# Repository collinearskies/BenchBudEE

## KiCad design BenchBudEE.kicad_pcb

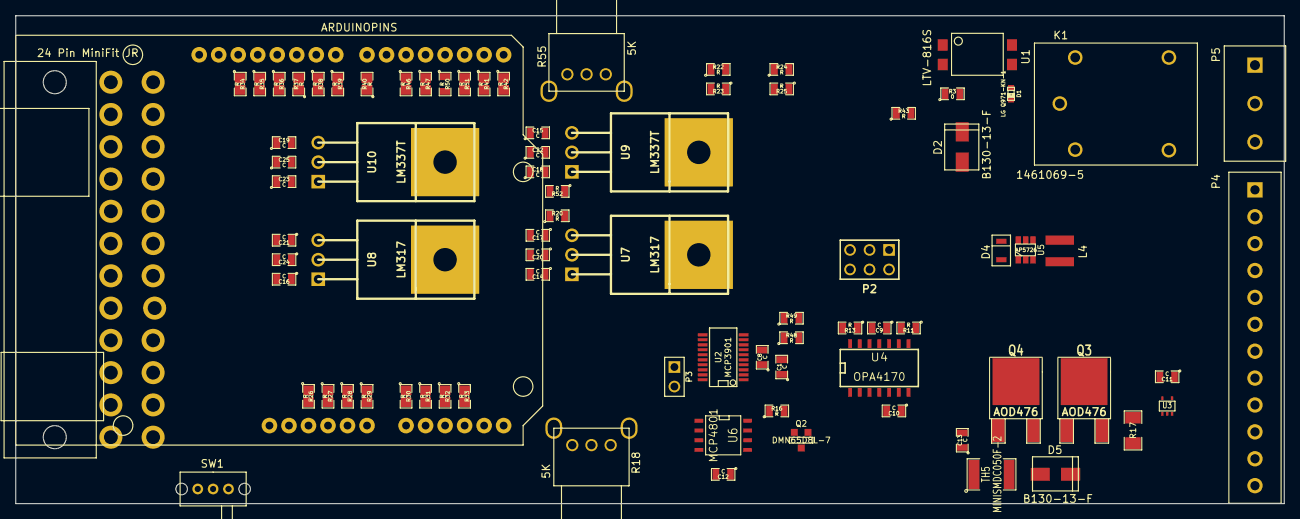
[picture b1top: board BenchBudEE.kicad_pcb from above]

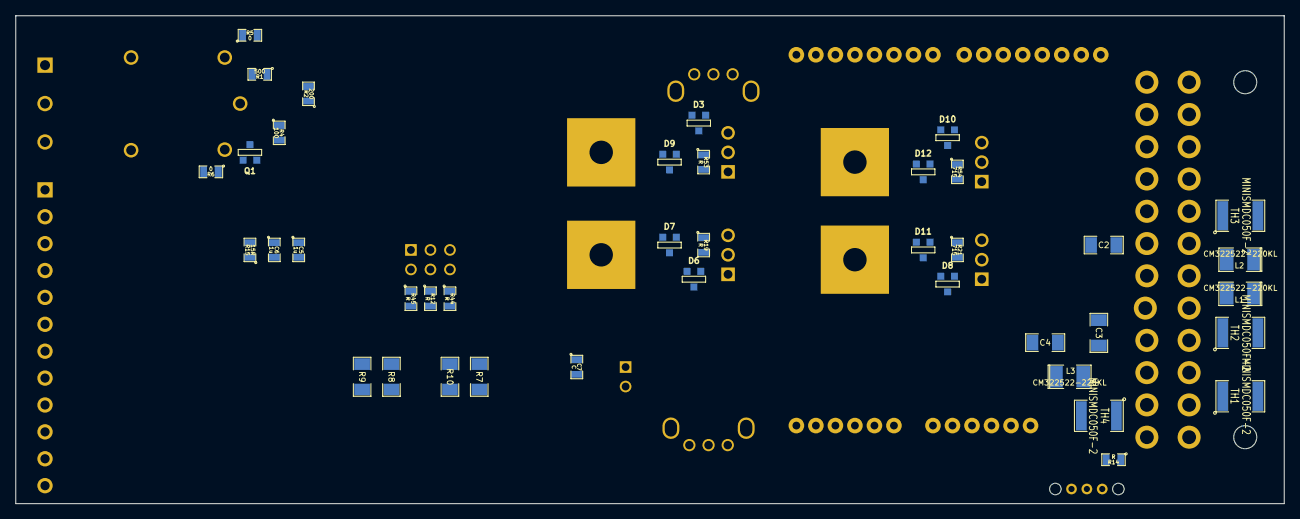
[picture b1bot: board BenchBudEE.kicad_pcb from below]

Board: 4 copper layers, 165.1 x 63.5 mm, 123 parts (40 on the bottom side), 96 nets, no tracks yet.

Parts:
ARD1: ARDUINOPINS; Arduino
C1, C7, C8, C9, C10, C11, C12, C13, C14, C15, C16, C17, C18, C19, C20, C21, C22, C23, C24, C25: C; SM0805
C2, C3, C4: C; SM1206
C5, C6: 1u; SM0805
D1: LG Q971-KN-1; LED-0603
D2, D5: B130-13-F; SMA
D3, D6, D7, D8, D9, D10, D11, D12: MMBD914-7-F; SOT23-DIODE
D4: B0540WS-7; SOD-323
K1: 1461069-5; TE-SPDT
L1, L2, L3: CM322522-220KL; SM1210L
L4: NR4012T220M; NR4012
P1: 24 Pin MiniFit JR; ATXheader
P2: CONN_3X2; pin_array_3x2
P3: CONN_2; PIN_ARRAY_2X1
P4: 12 Pin Terminal Block; 12pinTB
P5: 3 Pin TB; 3pinTB
Q1: 2N3904; SOT23EBC
Q2: DMN65D8L-7; SOT23GDS
Q3, Q4: AOD476; DPAK2
R1: 500; SM0805
R2: 200; SM0805
R3, R5, R6: 0; SM0805
R4: 100; SM0805
R7, R8, R9, R10, R17: R; SM1206
R11, R12, R13, R14, R16, R19, R20, R22, R23, R24, R25, R43, R44, R45, R48, R49, R50, R52, R53: R; SM0805
R15: 15R; SM0805
R18, R55: 5K; EVUE3K
R21, R54: 715; SM0805
R26, R27, R28, R29, R30, R31, R32, R33, R34, R35, R36, R37, R38, R39, R40, R41, R42, R46, R47, R51: R; SM0805-blob
SW1: Power Switch; BB_switch
TH1, TH2, TH3, TH4, TH5: MINISMDC050F-2; SM1812
U1: LTV-816S; 4-SMD
U2: MCP3901; SSOP20
U3: LMT84; SOT353
U4: OPA4170; SO14N
U5: AP5726; SOT23_6
U6: MCP4801; SO8N
U7, U8: LM317; TO220
U9, U10: LM337T; TO220

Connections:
+3.3V: P4.1, R14.2
+5P: L1.1, TH2.2
+5V: C2.1, C5.1, C7.2, C8.1, C11.1, C12.2, L1.2, L4.1, P4.2, R26.1, U2.2, U2.3, U3.4, U5.6, U6.1
+12C: C13.1, P1.10, TH3.1, TH5.1
+12P: L2.1, R3.2, R5.2, R29.1, TH3.2
+12V: C3.1, C10.2, C14.1, C16.1, D6.2, D8.2, L2.2, U4.4, U7.1, U8.1
-12P: L3.2, TH4.2
-12V: C4.2, C9.2, C15.2, C19.2, D3.1, D10.1, L3.1, U4.11, U9.2, U10.2
/Arduino/CURR_MEAS: Q3.2, Q4.3, R17.1, R32.1, U4.6
/Arduino/FAN_MODE: Q3.1, R42.2
/Arduino/FAN_PWM: Q2.G, R37.1
/Arduino/LED_EN_PWM: R38.2, U5.4
/Arduino/MISO: R36.2, U2.19
/Arduino/MOSI: R35.2, U2.20, U6.4
/Arduino/RELAY+: R41.2, U1.1
/Arduino/RELAY-: R1.1, R43.2
/Arduino/SCLK: R34.2, U2.18, U6.3
/Arduino/V+_ADJ_MON: R22.1, R23.2, R30.1
/Arduino/V-_ADJ_MON: R24.1, R25.2, R31.1
/Arduino/~DR: R47.2, U2.14
/Arduino/~LDAC: R50.2, U6.5
/Arduino/~RESET: R46.2, U2.1
/Arduino/~SHDN: R51.2, U6.6
/Fan/FAN_OUT+: D5.2, P4.8, TH5.2
/Fan/FAN_OUT-: D5.1, P4.9, Q4.2
/Fan/TACH_IN: P4.10, R33.1
/LED_Driver/LED_STRING+: C6.1, D4.2, P4.6, U5.5
/LED_Driver/LED_STRING-: P4.7, R15.1, U5.3
/PowerAdjustmentMonitor/V+_ADJ: C24.1, D8.1, D11.2, P4.4, R21.2, R22.2, U8.3
/PowerAdjustmentMonitor/V-_ADJ: C25.2, D10.2, D12.1, P4.5, R25.1, R54.1, U10.3
/Relay/RELAY_COM: K1.1, P5.2
/Relay/RELAY_NC: K1.4, P5.3
/Relay/RELAY_NO: K1.3, P5.1
/Thermocouple/CH0+: C1.1, R7.1, U2.4, U4.1
/Thermocouple/CH0-: C1.2, R49.2, U2.5
/Thermocouple/CH1+: U2.7, U3.3
/Thermocouple/CH1-: R48.2, U2.6
/Thermocouple/TC IN +: P4.11, U4.10
/Thermocouple/TC IN -: P4.12, U4.12
AGND: C7.1, C8.2, C9.1, C10.1, C11.2, C12.1, C13.2, C14.2, C15.1, C16.2, C17.2, C18.1, C19.1, C20.2, C21.2, C22.1, C23.1, C24.2, C25.1, Q2.S, Q3.3, R8.1, R17.2, R18.2, R20.1, R23.1, R24.2, R48.1, R49.1, R52.2, R55.2, U2.8, U2.11, U3.1, U3.2, U3.5, U6.7
FE_V+: C20.1, D6.1, D7.2, R19.2, U7.3
FE_V-: C22.2, D3.2, D9.1, R53.1, U9.3
GND: C2.2, C3.2, C4.1, C5.2, C6.2, P1.3, P1.5, P4.3, R2.2, R6.2, R15.2, R27.1, R28.1, R43.1, SW1.3, U5.2
unnamed: ARD1.18, R40.1
unnamed: ARD1.22, R36.1
unnamed: ARD1.24, R34.1
unnamed: ARD1.23, R35.1
unnamed: ARD1.6, R31.2
unnamed: ARD1.14, R50.1
unnamed: ARD1.4, R29.2
unnamed: ARD1.11, R42.1
unnamed: ARD1.20, R38.1
unnamed: ARD1.19, R39.1
unnamed: ARD1.12, R41.1
unnamed: ARD1.21, R37.2
unnamed: ARD1.5, R30.2
unnamed: ARD1.8, R33.2
unnamed: ARD1.7, R32.2
unnamed: ARD1.13, R51.1
unnamed: ARD1.15, R47.1
unnamed: ARD1.3, R28.2
unnamed: ARD1.2, R27.2
unnamed: ARD1.1, R26.2
unnamed: ARD1.16, R46.1
unnamed: P3.2, U2.13
unnamed: P3.1, U2.12
unnamed: R12.2, R13.1, R44.2, R45.2, U4.13
unnamed: P2.2, R45.1
unnamed: P2.4, R12.1
unnamed: P2.6, R44.1
unnamed: R9.2, R11.1, U4.8
unnamed: R10.2, R13.2, U4.14
unnamed: P2.1, P2.3, P2.5, R11.2, U4.9
unnamed: R7.2, R9.1, U4.2
unnamed: R8.2, R10.1, U4.3
unnamed: D2.2, K1.2, R5.1
unnamed: Q1.2, R4.2
unnamed: Q1.1, R6.1
unnamed: D1.1, R4.1, U1.3
unnamed: D1.2, R2.1
unnamed: D2.1, K1.5, Q1.3
unnamed: R1.2, U1.2
unnamed: R3.1, U1.4
unnamed: R14.1, SW1.1
unnamed: P1.16, SW1.2
unnamed: P1.14, TH4.1
unnamed: P1.4, P1.6, TH2.1
unnamed: P1.2, TH1.1
unnamed: D4.1, L4.2, U5.1
unnamed: R16.1, U6.8
unnamed: Q2.D, R16.2, U4.5
unnamed: Q4.1, U4.7
unnamed: C23.2, D12.2, R54.2, R55.1, U10.1
unnamed: C21.1, D11.1, R18.1, R21.1, U8.2
unnamed: C17.1, D7.1, R19.1, R20.2, U7.2
unnamed: C18.2, D9.2, R52.1, R53.2, U9.1

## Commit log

2014-02-02 Creation of schematic and layout files
2014-02-06 Created thermocouple schematic
2014-02-09 Created CurrentDriver, Relay, and PowerProtection modules
2014-02-09 Current driver refactoring, LED module, Arduino
2014-02-18 Refactoring and Created key shortcuts
2014-02-20 Relay module association and placement
2014-02-21 Thermocouple association and placement
2014-02-22 Terminal block and Arduino: assc/placement
2014-02-23 Fan driver: assc/placement
2014-02-23 Power protection and filter: assc/placement
2014-02-23 Power Adjustment: assc/placement
2014-02-24 LED driver: assc/placement
